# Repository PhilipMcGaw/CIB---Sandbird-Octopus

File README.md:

# CIB - Sandbird Octopus

Volt Free Contacts - Sandbird Octopus

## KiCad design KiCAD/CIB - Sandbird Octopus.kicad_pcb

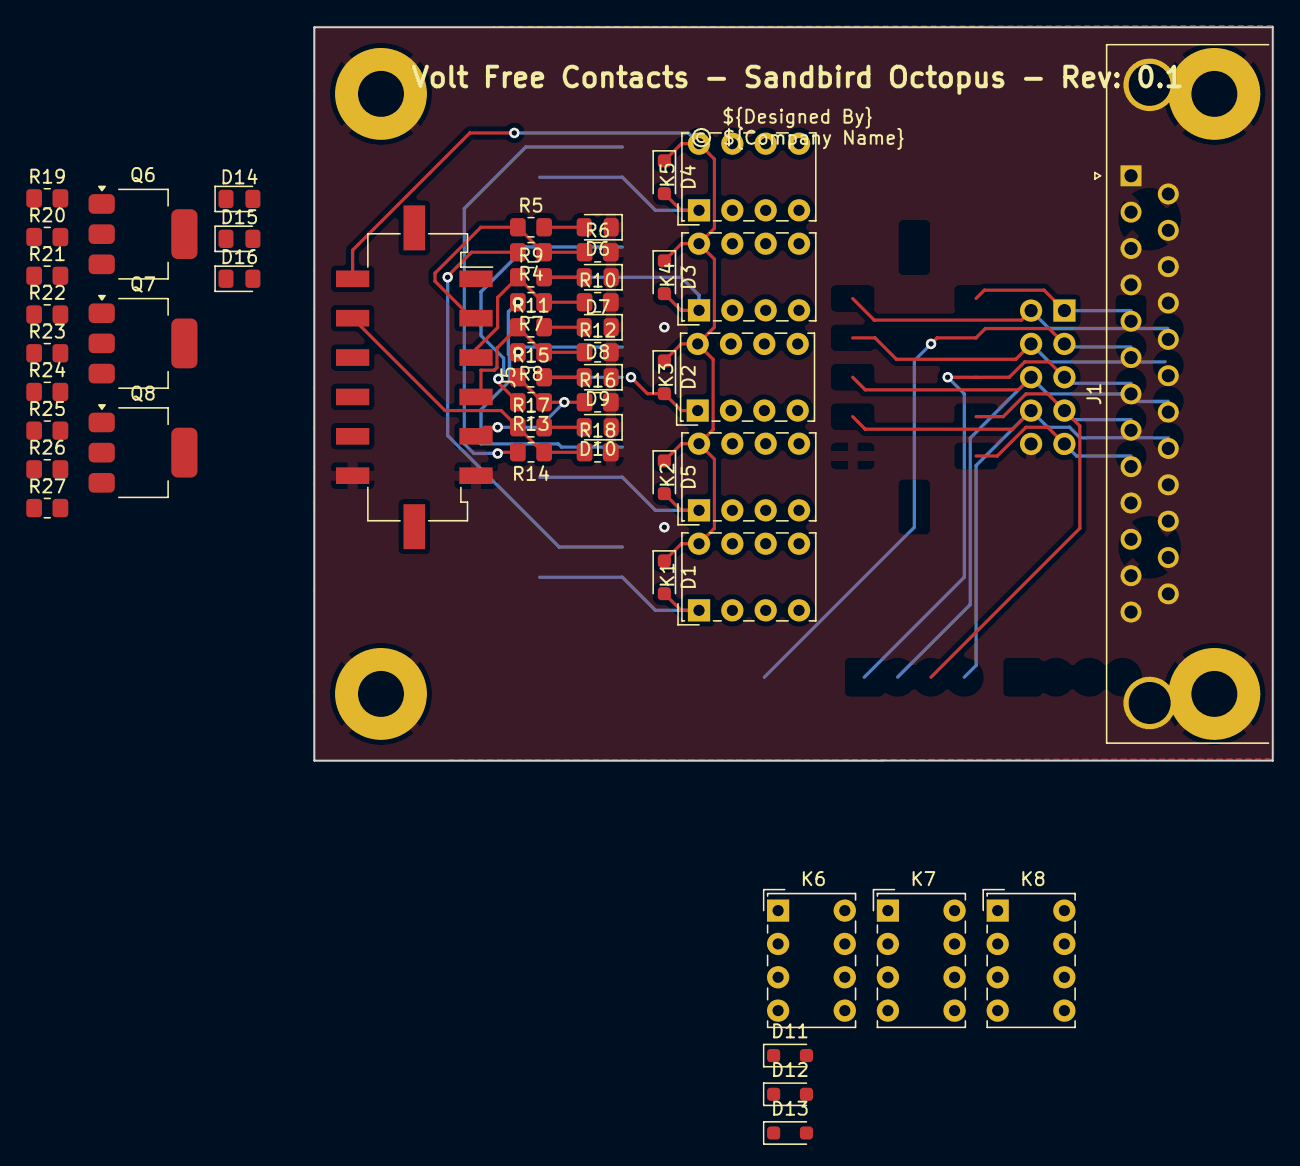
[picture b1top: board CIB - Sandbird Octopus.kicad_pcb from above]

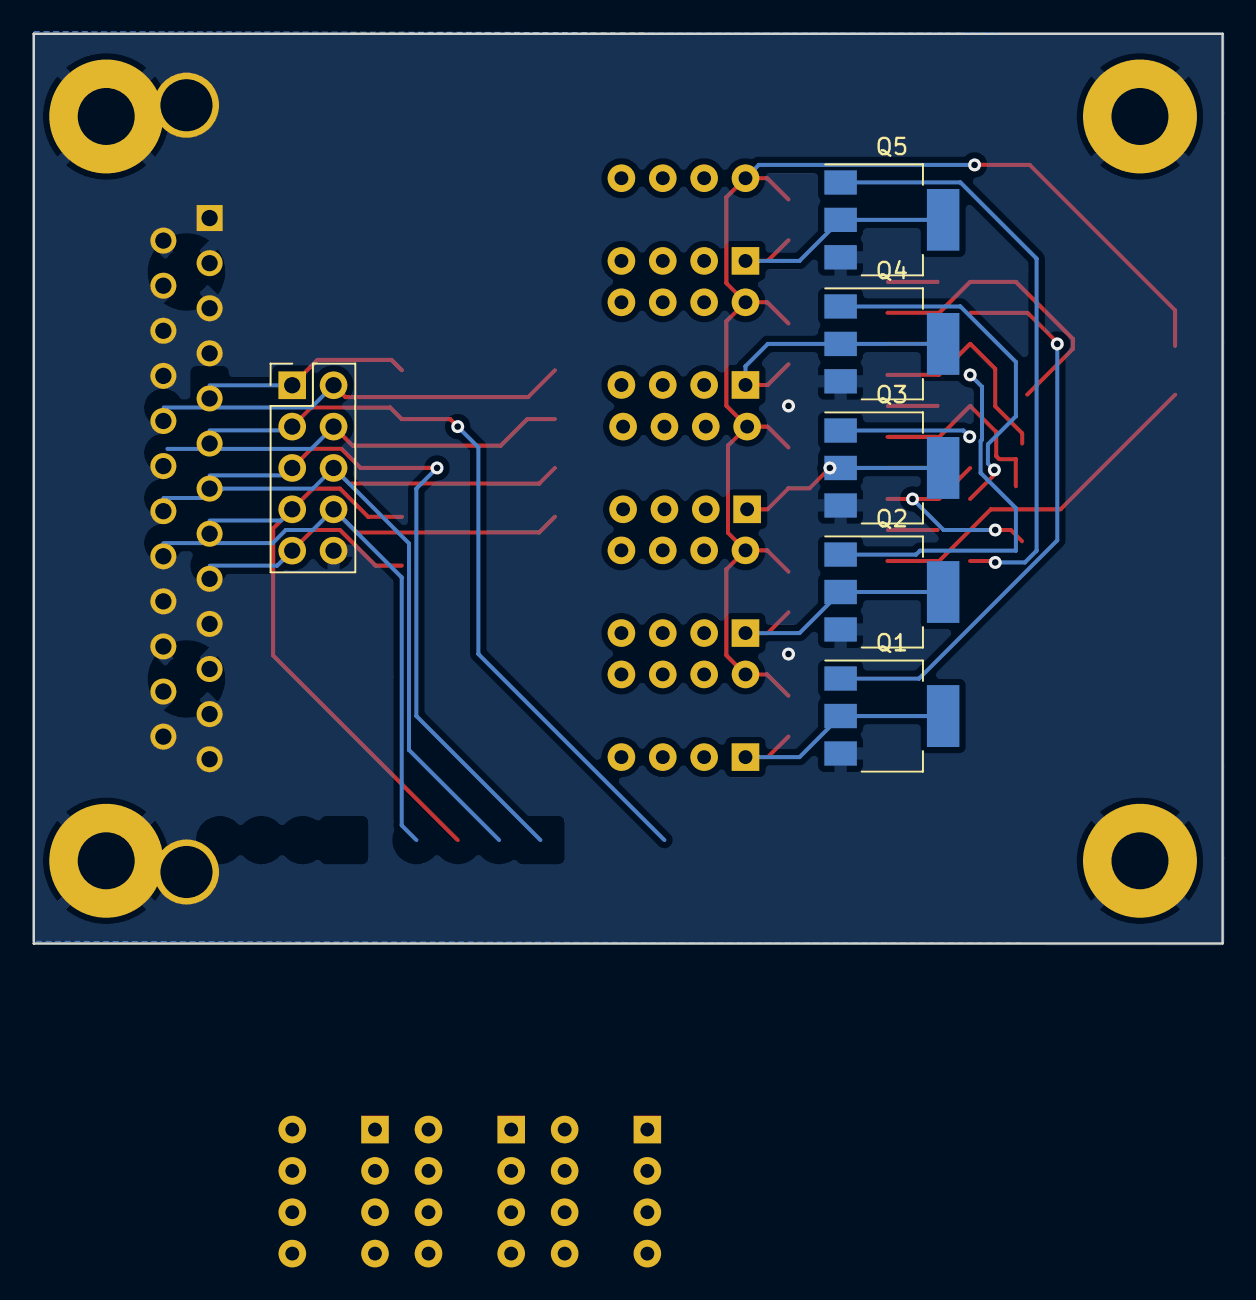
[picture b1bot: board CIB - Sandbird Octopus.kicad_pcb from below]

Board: 2 copper layers, 73.0 x 55.9 mm, 63 parts (6 on the bottom side), 58 nets.

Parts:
D1, D2, D3, D4, D5, D11, D12, D13: SBR130S3-7; D_SOD-323_HandSoldering
D6, D7, D8, D9, D10, D14, D15, D16: Red; LED_0805_2012Metric_Pad1.15x1.40mm_HandSolder
H1, H2, H3, H4: MountingHole; MountingHole_3.5mm_Pad
J1: DB25; DSUB-25_Socket_Horizontal_P2.77x2.84mm_EdgePinOffset7.70mm_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
J5: Enable; Molex_Micro-Fit_3.0_43045-1218_2x06-1MP_P3.00mm_Vertical
J6: Conn_01x26_Pin; PinHeader_2x05_P2.54mm_Vertical
K1, K2, K3, K4, K5, K6, K7, K8: Relay_DPDT_Omron_G6K-2P
Q1, Q2, Q3, Q4, Q5, Q6, Q7, Q8: STN3NF06; SOT-223-3_TabPin2
R4, R5, R7, R8, R9, R11, R13, R14, R15, R17, R19, R21, R22, R24, R25, R27: 1k; R_0805_2012Metric_Pad1.20x1.40mm_HandSolder
R6, R10, R12, R16, R18, R20, R23, R26: 10k; R_0805_2012Metric_Pad1.20x1.40mm_HandSolder

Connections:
+12V: D1.1 (K), D2.1 (K), D3.1 (K), D4.1 (K), D5.1 (K), D11.1 (K), D12.1 (K), D13.1 (K), J5.7, K1.8, K2.8, K3.8, K4.8, K5.8, K6.8, K7.8, K8.8
/Pin_01: J1.1, J6.1, K1.5
/Pin_02: J1.2, J6.3, K1.7
/Pin_03: J1.3, J6.5, K1.3
/Pin_04: J1.4, J6.7, K2.5
/Pin_05: J1.5, J6.9, K2.7
/Pin_06: J1.6, K2.3
/Pin_07: J1.7, K3.5
/Pin_08: J1.8, K3.7
/Pin_09: J1.9, K3.3
/Pin_10: J1.10, K4.5
/Pin_11: J1.11, K4.7
/Pin_12: J1.12, K4.3
/Pin_14: J1.14, J6.2, K1.6
/Pin_15: J1.15, J6.4, K1.4
/Pin_16: J1.16, J6.6, K1.2
/Pin_17: J1.17, J6.8, K2.6
/Pin_18: J1.18, J6.10, K2.4
/Pin_19: J1.19, K2.2
/Pin_20: J1.20, K3.6
/Pin_21: J1.21, K3.4
/Pin_22: J1.22, K3.2
/Pin_23: J1.23, K4.6
/Pin_24: J1.24, K4.4
/Pin_25: J1.25, K4.2
/Relay_1: D1.2 (A), K1.1, Q1.2 (D)
/Relay_1_en: J5.2, R4.1, R5.1, R6.1
/Relay_2: D5.2 (A), K2.1, Q2.2 (D)
/Relay_2_en: J5.3, R7.1, R9.1, R10.1
/Relay_3: D2.2 (A), K3.1, Q3.2 (D)
/Relay_3_en: J5.4, R8.1, R11.1, R12.1
/Relay_4: D3.2 (A), K4.1, Q4.2 (D)
/Relay_4_en: J5.5, R13.1, R15.1, R16.1
/Relay_5: D4.2 (A), K5.1, K5.2, K5.4, K5.5, K5.7, Q5.2 (D)
/Relay_5_en: J5.8, R14.1, R17.1, R18.1
/Relay_6: D11.2 (A), K6.1, Q6.2 (D)
/Relay_6_en: J5.9, R19.1, R20.1, R21.1
/Relay_7: D12.2 (A), K7.1, Q7.2 (D)
/Relay_7_en: J5.10, R22.1, R23.1, R24.1
/Relay_8: D13.2 (A), K8.1, Q8.2 (D)
/Relay_8_en: J5.11, R25.1, R26.1, R27.1
GND: D6.1 (K), D7.1 (K), D8.1 (K), D9.1 (K), D10.1 (K), D14.1 (K), D15.1 (K), D16.1 (K), H1.1 (1_1), H2.1 (1_1), H3.1 (1_1), H4.1 (1_1), J1.SH (PAD), J5.6, J5.12, Q1.3 (S), Q2.3 (S), Q3.3 (S), Q4.3 (S), Q5.3 (S), Q6.3 (S), Q7.3 (S), Q8.3 (S), R6.2, R10.2, R12.2, R16.2, R18.2, R20.2, R23.2, R26.2
unnamed: D6.2 (A), R5.2
unnamed: D7.2 (A), R9.2
unnamed: D8.2 (A), R11.2
unnamed: D9.2 (A), R15.2
unnamed: D10.2 (A), R17.2
unnamed: D14.2 (A), R19.2
unnamed: D15.2 (A), R22.2
unnamed: D16.2 (A), R25.2
unnamed: Q1.1 (G), R4.2
unnamed: Q2.1 (G), R7.2
unnamed: Q3.1 (G), R8.2
unnamed: Q4.1 (G), R13.2
unnamed: Q5.1 (G), R14.2
unnamed: Q6.1 (G), R21.2
unnamed: Q7.1 (G), R24.2
unnamed: Q8.1 (G), R27.2
